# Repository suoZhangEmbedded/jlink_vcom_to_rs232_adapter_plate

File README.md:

# jlink_vcom_to_rs232_adapter_plate
# jlink 虚拟串口 转 RS232接口 转接板

1、jlink to 232 功能 接口 DB9 公口

2、jlink 转 SWD 接口 XH-4A

3、jlink 转 swd 接口 XH-6A

4、jlink 转 ttl 接口 XH-3A

5、232 接口 XH-3A

6、完整的 jlink 20pin 接口转接

7、[jlink 20 pin 接口描述](https://www.segger.com/products/debug-probes/j-link/technology/interface-description/)

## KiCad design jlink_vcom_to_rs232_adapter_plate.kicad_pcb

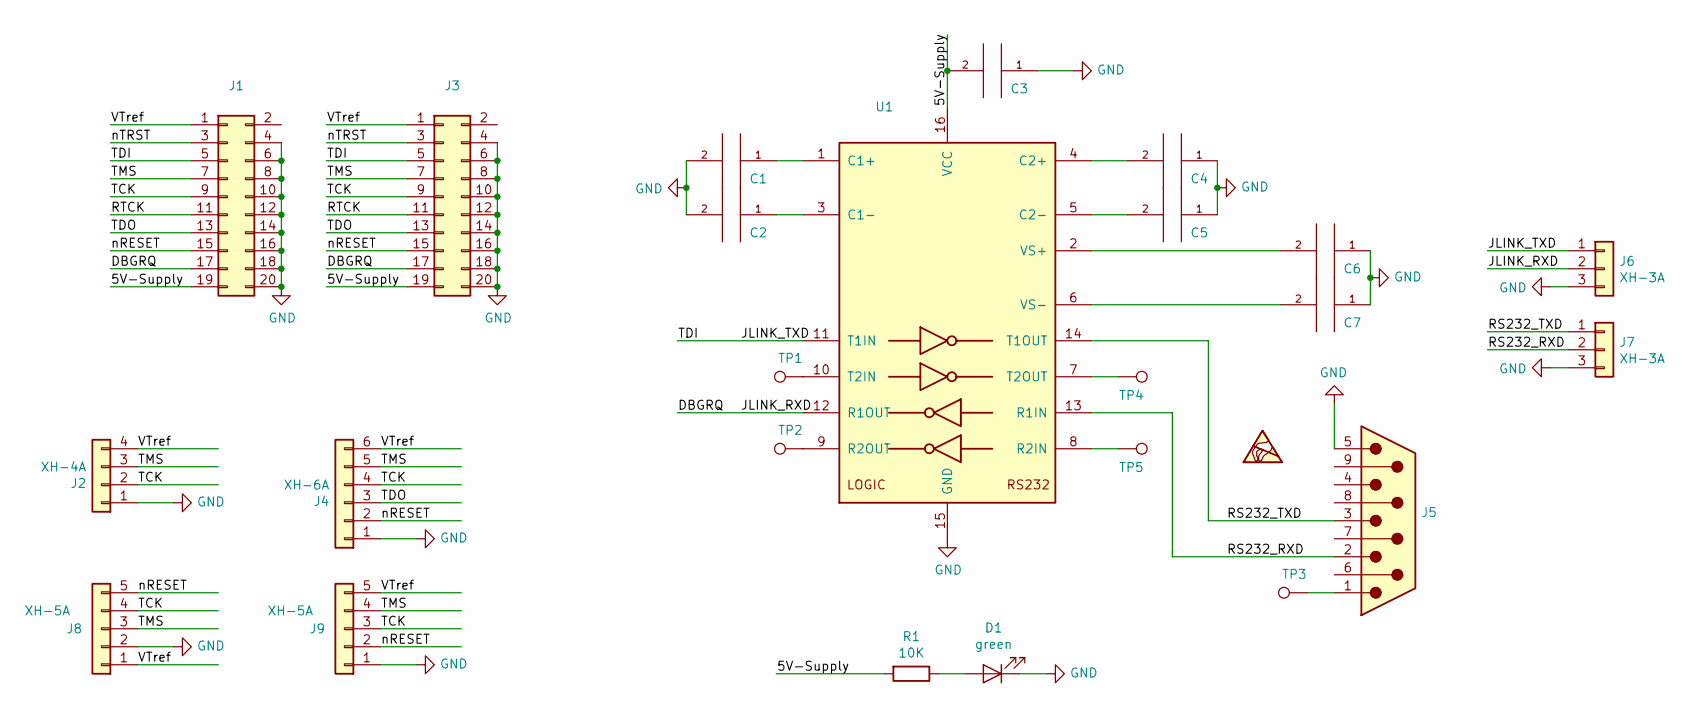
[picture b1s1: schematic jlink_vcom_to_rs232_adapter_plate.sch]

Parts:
C1, C2, C3, C4, C5, C6, C7: 220nF(224) ±10% 16V; C_0805_2012Metric
D1: green; LED_0805_2012Metric
J1: 排母 2*10P 2.54mm 弯针; PinSocket_2x10_P2.54mm_Horizontal
J2: XH-4A; JST_XH_B4B-XH-A_1x04_P2.50mm_Vertical
J3: 2.54mm 2*10P 直 简牛; IDC-Header_2x10_P2.54mm_Vertical
J4: XH-6A; JST_XH_B6B-XH-A_1x06_P2.50mm_Vertical
J5: DMR-XP 公头叉锁 9P 半金; DSUB-9_Male_Horizontal_P2.77x2.84mm_EdgePinOffset9.90mm_Hou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
J6, J7: XH-3A; JST_XH_B3B-XH-A_1x03_P2.50mm_Vertical
J8, J9: XH-5A; JST_XH_B5B-XH-A_1x05_P2.50mm_Vertical
R1: 10K; R_0805_2012Metric
TP1, TP2, TP3, TP4, TP5: TestPoint; TestPoint_Pad_D1.0mm
U1: UT3232G-S16-R; SOP-16_4.4x10.4mm_P1.27mm

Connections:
/5V-Supply: C3.2, J1.19, J3.19, R1.2, U1.16 (VCC)
/DBGRQ: J1.17, J3.17, J6.2, U1.12 (R1OUT)
/JLINK_TXD: J1.5, J3.5, J6.1, U1.11 (T1IN)
/RS232_RXD: J5.2, J7.2, U1.13 (R1IN)
/RS232_TXD: J5.3, J7.1, U1.14 (T1OUT)
/RTCK: J1.11, J3.11
/TCK: J1.9, J2.2, J3.9, J4.4, J8.4, J9.3
/TDO: J1.13, J3.13, J4.3
/TMS: J1.7, J2.3, J3.7, J4.5, J8.3, J9.4
/VTref: J1.1, J2.4, J3.1, J4.6, J8.1, J9.5
/nRESET: J1.15, J3.15, J4.2, J8.5, J9.2
/nTRST: J1.3, J3.3
GND: C1.2, C2.2, C3.1, C4.1, C5.1, C6.1, C7.1, D1.1 (K), J1.4, J1.6, J1.8, J1.10, J1.12, J1.14, J1.16, J1.18, J1.20, J2.1, J3.4, J3.6, J3.8, J3.10, J3.12, J3.14, J3.16, J3.18, J3.20, J4.1, J5.5, J6.3, J7.3, J8.2, J9.1, U1.15 (GND)
unnamed: C1.1, U1.1 (C1+)
unnamed: C2.1, U1.3 (C1-)
unnamed: C4.2, U1.4 (C2+)
unnamed: C5.2, U1.5 (C2-)
unnamed: C6.2, U1.2 (VS+)
unnamed: C7.2, U1.6 (VS-)
unnamed: D1.2 (A), R1.1
unnamed: J5.1, TP3.1
unnamed: TP1.1, U1.10 (T2IN)
unnamed: TP2.1, U1.9 (R2OUT)
unnamed: TP4.1, U1.7 (T2OUT)
unnamed: TP5.1, U1.8 (R2IN)

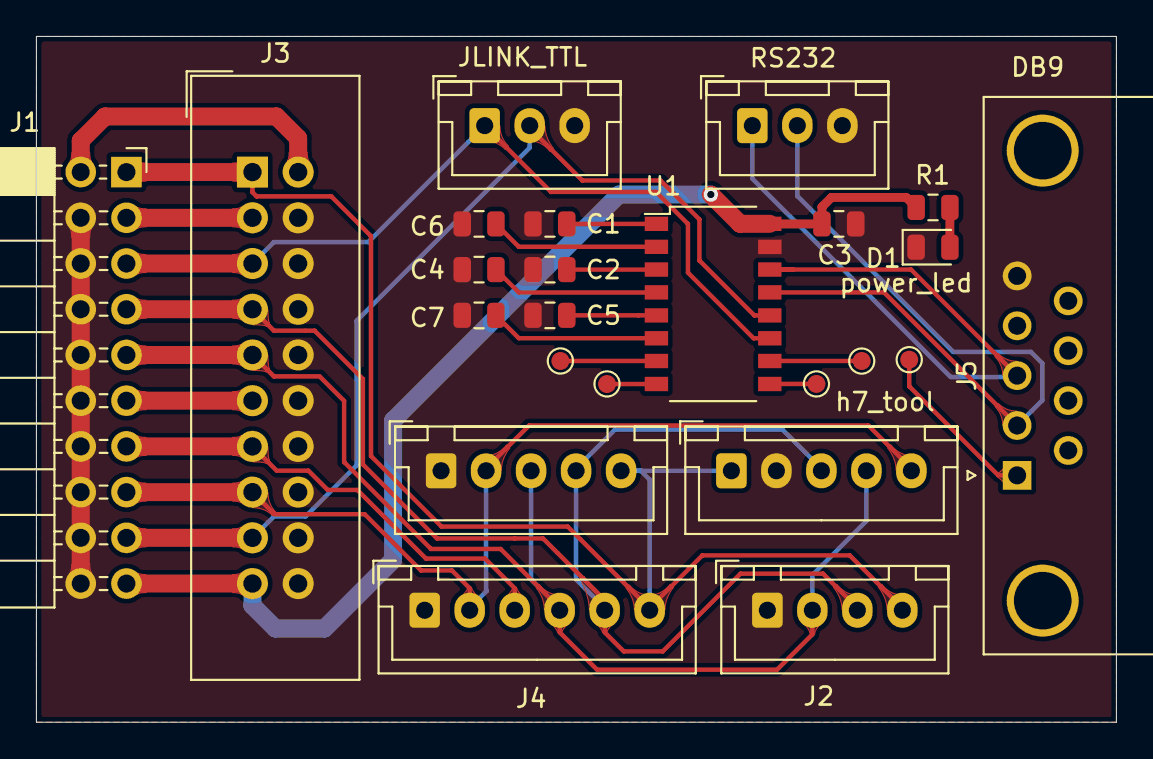
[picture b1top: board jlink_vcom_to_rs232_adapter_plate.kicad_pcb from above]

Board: 2 copper layers, 60.0 x 38.1 mm, 24 parts (0 on the bottom side), 25 nets.

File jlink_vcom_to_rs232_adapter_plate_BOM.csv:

"Comment","Description","Designator","Footprint","LibRef","Pins","Quantity","PartNumber","url",
"220nF(224) ±10% 16V","desc","C7,C6,C5,C4,C3,C2,C1,","C_0805_2012Metric","libref","2","7","","",
"green","desc","D1,","LED_0805_2012Metric","libref","2","1","","",
"10K","desc","R1,","R_0805_2012Metric","libref","2","1","","",
"TestPoint","desc","TP5,TP4,TP3,TP2,TP1,","TestPoint_Pad_D1.0mm","libref","1","5","","",
"UT3232G-S16-R","desc","U1,","SOP-16_4.4x10.4mm_P1.27mm","libref","16","1","","",
"Through Hole Items ",
"排母 2*10P 2.54mm 弯针","desc","J1,","PinSocket_2x10_P2.54mm_Horizontal","libref","20","1","","",
"XH-4A","desc","J2,","JST_XH_B4B-XH-A_1x04_P2.50mm_Vertical","libref","4","1","","",
"2.54mm 2*10P 直 简牛","desc","J3,","IDC-Header_2x10_P2.54mm_Vertical","libref","20","1","","",
"XH-6A","desc","J4,","JST_XH_B6B-XH-A_1x06_P2.50mm_Vertical","libref","6","1","","",
"DMR-XP 公头叉锁 9P 半金","desc","J5,","DSUB-9_Male_Horizontal_P2.77x2.84mm_EdgePinOffset9.90mm_Housed_MountingHolesOffset11.32mm","libref","11","1","","",
"XH-3A","desc","J7,J6,","JST_XH_B3B-XH-A_1x03_P2.50mm_Vertical","libref","3","2","","",
"XH-5A","desc","J9,J8,","JST_XH_B5B-XH-A_1x05_P2.50mm_Vertical","libref","5","2","","",

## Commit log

2019-11-07 1、.gitignore文件添加 2、jlink to 232 功能 ok 3、jlink 转 SWD 接口 XH-4A 4、jlink 转 swd 接口 XH-6A 5、jlink 转 ttl 接口 XH-3A 6、232 接口 XH-3A 7、完整的 jlink 20pin 接口
2019-11-07 1、增加 README.md 图片效果显示
2019-11-07 1、修改 图片
2019-11-07 1、修改图片尺寸
2019-11-07 1、修改图片位置
2019-11-07 1、增加 H7_TOOL 专用 SWD 接口 2、增加 XH-5A 接口
2019-11-07 1、更新 图片
2019-11-07 1、增加 电源 LED 灯 指示 2、布线 完成 3、泪滴 增加完成 4、覆铜 完成
2019-11-07 1、更新 README 图片 为最新图片
2019-11-11 1、修改 每个 元器件 为实际的 value 2、生成了 geber 文件
